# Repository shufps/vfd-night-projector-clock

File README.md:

# vfd-night-clock

## Description

The VFD Night Projector Clock is the first and only (at the moment and to my knowledge 😁) night projecting clock that uses a VFD display.

When receiving one of the NOS IVL2-7/5 displays, I noticed that the illuminated area could fit in about full-format (24x36mm) what was standard in analogue photography.

For this reason there are plenty of old lenses (e.g. with M42 threading) out there that almost cost nothing anymore although they have impressive technical properties like 1:2.8 with f=135.

Moreover, they have a flange focal distance of 45.46mm which allows to build a relatively compact casing.

So here it is ... 🥳

This image shows a comparison between my old radio clock with projector and the VFD night clock projector:

The brighness is perfect in the night 👌 (but ofc barely visible at day)

If everything is adjusted properly, you even can see the grid on the digits:

## Properties

There are some methods how a VFD can be operated. After some prior experience with VFDs this is one of the easiest methods:

- isolated 24 DCDC converter for anode voltage. The V+ is connected to GND, so you have -24V on the board
- the positive gate/segment voltage is +3.3V. You easily can switch the positive gate/segment voltage with BSS84s from a STM32 with no additional parts what is the easiest solution. This gives a total gate / segment voltage of 27.3V
- AC Filament drive is done with a full-bridge made of a two channel MOSFET driver. The output is AC coupled and pulled to about -22V. Bias is adjustable (even could be used to change the brightness)

## STM32 Software

The STM32 software currently only supports a json-rpc via USB virtual COM port (CDC). Buttons are currently unused 🙈

There is python code that can 

- measure the clock accuracy
- set the time
- set the display state and auto-switch on/off

This are small examples that nicely demonstrate how to use the json-rpc.

## 3D case

The case was designed in a way that no supports are needed. The upper part is simply clipped on the lower part.

<!--
Ode to VFD Displays (Chatti4 2023)

Oh, relics of an era long past,<br>
Vacuum Fluorescent Displays, you hold fast.<br>
Born in Soviet realms, a technological feast,<br>
Your glasspunk aesthetics have never ceased.<br>

In your cylindrical tubes, a dance of light,<br>
A greenish-blue hue, softly bright.<br>
Your glow, a whisper from history's tide,<br>
In old devices, you reside with pride.<br>

You are the silent storytellers, bold,<br>
Of times when technology wasn't so cold.<br>
Your luminescent charm, a visual delight,<br>
In the stillness of rooms, you're the night's light.<br>

Through you, numbers and words gracefully flow,<br>
A retro display, a nostalgic glow.<br>
Your enduring spirit, a testament to time,<br>
In the world of screens, you're a verse, a rhyme.<br>

VFD, in your glass cocoon you lay,<br>
A visual symphony in green and gray.<br>
A bridge from the past, to the present you lead,<br>
A piece of history, in every glowing bead.<br>

In the march of progress, you're a quiet ode,<br>
A reminder of a less digital road.<br>
VFD displays, in you, the past does reside,<br>
A beautiful, forgotten technological stride.<br>
-->

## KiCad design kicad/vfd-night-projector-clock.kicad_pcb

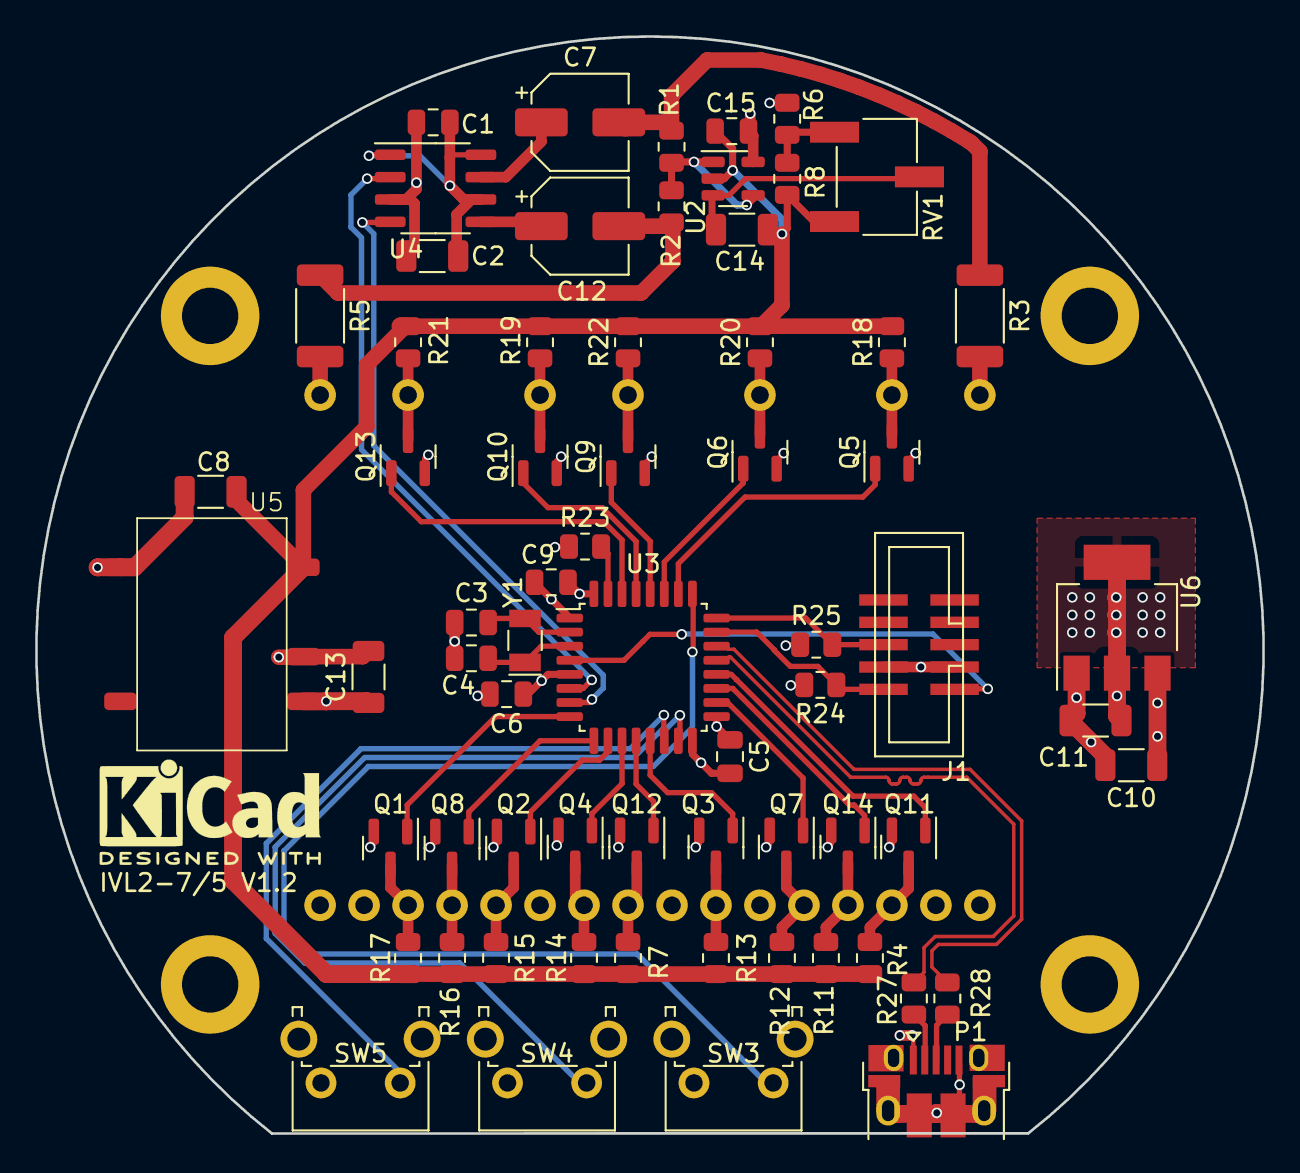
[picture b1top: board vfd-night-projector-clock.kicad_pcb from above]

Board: 4 copper layers, 69.7 x 62.3 mm, 67 parts (1 on the bottom side), 56 nets.

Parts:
C1, C5, C6, C9, C15: 100n; C_0805_2012Metric
C2, C8, C10, C11, C13: 10µF/50V; C_1206_3216Metric
C3, C4: 6pF; C_0805_2012Metric
C7, C12: 10µ/50V; CP_Elec_5x5.4
C14: 1µ/50V; C_1206_3216Metric
J1: SWD; PinHeader_IDC_2x05_P1.27mm_Vertical_SMD
P1: MYUSB_B; USB_Micro-B_Amphenol_10103594-0001LF_Horizontal
Q1, Q2, Q3, Q4, Q5, Q6, Q7, Q8, Q9, Q10, Q11, Q12, Q13, Q14: BSS84; SOT-23
R1, R2: 1k; R_0805_2012Metric
R3, R5: 15R; R_2010_5025Metric
R4, R7, R11, R12, R13, R14, R15, R16, R17, R18, R19, R20, R21, R22: 47k; R_0805_2012Metric
R6: 36k; R_0805_2012Metric
R8: x; R_0805_2012Metric
R23: 100k; R_0805_2012Metric
R24, R25: 10k; R_0805_2012Metric
R27, R28: 22; R_0805_2012Metric
RV1: 10k; Potentiometer_Bourns_3269W_Vertical
SW3, SW4, SW5: SW_SPST; SW_Tactile_SPST_Angled_PTS645Vx83-2LFS
U1: IVL2-7_5; ILV2-5_7
U2: TLV9301xDBV; SOT-23-5
U3: STM32L052K6Tx; LQFP-32_7x7mm_P0.8mm
U4: 2EDN7524F; SO-8_3.9x4.9mm_P1.27mm
U5: IES0105S24; IES0105S24-dcdc
U6: LM1117MP-3.3; SOT-223-3_TabPin2
Y1: Crystal; Crystal_SMD_EuroQuartz_EQ161-2Pin_3.2x1.5mm

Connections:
+3V3: C5.1, C6.1, C9.1, C11.1, Q1.2 (S), Q2.2 (S), Q3.2 (S), Q4.2 (S), Q5.2 (S), Q6.2 (S), Q7.2 (S), Q8.2 (S), Q9.2 (S), Q10.2 (S), Q11.2 (S), Q12.2 (S), Q13.2 (S), Q14.2 (S), R24.2, U3.1 (VDD), U3.5 (VDDA), U3.17 (VDD), U6.2 (VO)
+5V: C1.1, C2.2, C10.1, C13.2, P1.1 (VCC), U4.1 (ENA), U4.6 (VDD), U4.8 (ENB), U5.2 (+VIN), U6.3 (VI)
-24V: C8.1, C14.2, C15.2, R4.2, R7.2, R8.1, R11.2, R12.2, R13.2, R14.2, R15.2, R16.2, R17.2, R18.2, R19.2, R20.2, R21.2, R22.2, RV1.3, U2.2 (V-), U5.4 (-VOUT)
/GATE_1: Q5.3 (D), R18.1, U1.22 (C1)
/GATE_2: Q6.3 (D), R20.1, U1.21 (C2)
/GATE_3: Q9.3 (D), R22.1, U1.20 (C3)
/GATE_4: Q10.3 (D), R19.1, U1.19 (C4)
/GATE_5: Q13.3 (D), R21.1, U1.18 (C5)
/LL_GATE_1: Q5.1 (G), U3.26 (PB3)
/LL_GATE_2: Q6.1 (G), U3.27 (PB4)
/LL_GATE_3: Q9.1 (G), U3.28 (PB5)
/LL_GATE_4: Q10.1 (G), U3.29 (PB6)
/LL_GATE_5: Q13.1 (G), U3.30 (PB7)
/LL_SEG_A: Q1.1 (G), U3.8 (PA2)
/LL_SEG_B: Q2.1 (G), U3.10 (PA4)
/LL_SEG_C: Q3.1 (G), U3.13 (PA7)
/LL_SEG_D: Q4.1 (G), U3.11 (PA5)
/LL_SEG_DP1: Q11.1 (G), U3.20 (PA10)
/LL_SEG_DP2: Q12.1 (G), U3.12 (PA6)
/LL_SEG_E: Q7.1 (G), U3.18 (PA8)
/LL_SEG_F: Q8.1 (G), U3.9 (PA3)
/LL_SEG_G: Q14.1 (G), U3.19 (PA9)
/SEG_A: Q1.3 (D), R17.1, U1.14 (a)
/SEG_B: Q2.3 (D), R15.1, U1.12 (b)
/SEG_C: Q3.3 (D), R13.1, U1.7 (c)
/SEG_D: Q4.3 (D), R14.1, U1.10 (d)
/SEG_DP1: Q11.3 (D), R4.1, U1.3 (DP1)
/SEG_DP2: Q12.3 (D), R7.1, U1.9 (DP2)
/SEG_E: Q7.3 (D), R12.1, U1.5 (e)
/SEG_F: Q8.3 (D), R16.1, U1.13 (f)
/SEG_G: Q14.3 (D), R11.1, U1.4 (g)
ARM_NRST: J1.1, U3.4 (NRST)
ARM_SWCLK: J1.6, R25.2, U3.24 (PA14)
ARM_SWDIO: J1.2, R24.1, U3.23 (PA13)
FIL1: R3.2, U1.23 (F1)
FIL2: R5.2, U1.17 (F2)
FILDRV1: U3.6 (PA0), U4.2 (INA)
FILDRV2: U3.7 (PA1), U4.4 (INB)
GND: C1.2, C2.1, C3.1, C4.1, C5.2, C6.2, C8.2, C9.2, C10.2, C11.2, C13.1, C15.1, J1.3, J1.4, P1.5 (GND), P1.6 (shield), R6.2, R23.1, R25.1, SW3.2 (B), SW4.2 (B), SW5.2 (B), U2.5 (V+), U3.16 (VSS), U3.32 (VSS), U4.3 (GND), U5.1 (-VIN), U5.5 (+VOUT), U6.1 (GND)
unnamed: C7.2, R1.2, R3.1
unnamed: C12.2, R2.1, R5.1
unnamed: P1.3 (D+), R28.2
unnamed: P1.2 (D-), R27.2
unnamed: R6.1, R8.2, RV1.1
unnamed: C14.1, RV1.2, U2.3 (+)
unnamed: R1.1, R2.2, U2.1, U2.4 (-)
unnamed: R23.2, U3.31 (BOOT0)
unnamed: C3.2, U3.2 (PC14), Y1.2
unnamed: C4.2, U3.3 (PC15), Y1.1
unnamed: C7.1, U4.7 (OUTA)
unnamed: C12.1, U4.5 (OUTB)
SW1: SW3.1 (A), U3.25 (PA15)
SW2: SW4.1 (A), U3.15 (PB1)
SW3: SW5.1 (A), U3.14 (PB0)
USB_D+: R28.1, U3.22 (PA12)
USB_D-: R27.1, U3.21 (PA11)

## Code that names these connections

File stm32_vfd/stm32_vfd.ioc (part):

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Mcu.UserName=STM32L052K6Tx
PA11.Mode=Device
RCC.SYSCLKSource=RCC_SYSCLKSOURCE_PLLCLK
PA12.Signal=USB_DP
PB6.Signal=GPIO_Output
PC14-OSC32_IN.Mode=LSE-External-Oscillator
PA14.Mode=Serial_Wire
PB7.Signal=GPIO_Output
PA8.Signal=GPIO_Output
PA0.Signal=S_TIM2_CH1
Mcu.Package=LQFP32
PB1.Signal=GPIO_Input
PA6.Signal=GPIO_Output
PA10.Signal=GPIO_Output
PA15.Signal=GPIO_Input
PB4.Signal=GPIO_Output
PA3.Signal=GPIO_Output
PC15-OSC32_OUT.Mode=LSE-External-Oscillator
PC14-OSC32_IN.Signal=RCC_OSC32_IN
PA13.Signal=SYS_SWDIO
PA9.Signal=GPIO_Output
PC15-OSC32_OUT.Signal=RCC_OSC32_OUT
PA1.Signal=S_TIM2_CH2
PA5.Signal=GPIO_Output
board=custom
PA13.Mode=Serial_Wire
Mcu.Name=STM32L052K(6-8)Tx
PA2.Signal=GPIO_Output
PB3.Signal=GPIO_Output
PA4.Signal=GPIO_Output
RCC.SYSCLKFreq_VALUE=32000000
PB5.Signal=GPIO_Output
PA12.Mode=Device
PA11.Signal=USB_DM
PA14.Signal=SYS_SWCLK
PB0.Signal=GPIO_Input
PA7.Signal=GPIO_Output

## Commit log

2023-11-14 added order list for digikey
2023-11-14 removed old code
